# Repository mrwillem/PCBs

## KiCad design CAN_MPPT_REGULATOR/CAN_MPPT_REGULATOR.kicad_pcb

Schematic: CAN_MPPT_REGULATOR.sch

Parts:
AFF1: QBDS20zzzz; 7SEGMENT-LED_DUAL_QBDS200R
C1, C3, C4: C; C_0805
C2: 2nFC; C_0805
C5: 470nF; C_0805
C6, C34: 1uF; C_0805
C7, C8: 1uF 0805ZC105KAT2A; C_0805
C9: 2,2 uF; C_0805
C10, C18: 10nF; C_0603
C11, C14, C17, C21, C24, C25, C26, C27, C28, C29, C30, C35, C43, C44, C45, C46, C47, C72, C75: 100nF; C_0603
C12, C15: 2uF; C_0805
C13, C31: 4,7uF; C_0805
C16, C38: 33uF; CP_Elec_6.3x7.7
C19, C20: 22pF; C_0603
C22, C23: C; C_0603
C32: 2,2uF; C_0805
C33, C40, C42, C53: 1uF GRM219R71E105KA88D; C_0805
C36: C
C37: 100pF 60V; C_0805
C41: 10nF; C_0805
C51: 100nF; C_0805
C52: 1nF; C_0805
C60, C61, C62, C63: 10uF; C_0805
C70, C71, C73, C74: 4.7uF GRM31CR71H47; C_1206
CB1, CB2: 68 uF EEE-FK1J680UP; CP_Elec_8x10.5
CB3, CB4: B41888E8687M000; CP_Radial_D18.0mm_P7.50mm
CBIA1: 1 uF GRM219R71E105KA88D; C_0805
CBO1, CBO2: 100nF; C_0805
CCOMP1: 27nF 12065A272JAT2A; C_0805
CCOMP2: 47pF CL21C470JBANNNC; C_0805
CF1: 220nF C1608X5R1H224K080AB; C_0805
CIN1, CIN2, CIN3, CIN4, CIN5, CIN6, CIN7, CIN8, CIN9, CIN10: 10uF C3216X5R1H106K160AB; C_1206
COUT1, COUT2, COUT3, COUT4, COUT5, COUT6, COUT7, COUT8, COUT9, COUT10, COUT11, COUT12: 10 uF CL31A106MBHNNNE; C_1206
CSG1, CSG2, CSG3: 47pF 06035A470JAT2A; C_0603
CSL1: 91pF CL10C910JB8NCNC; C_0603
CSS1: 22nF gcm21b5c1h223ja16l; C_0805
CVCC1: 1 uF EMK107B7105KA-T; C_0603
D1, D6, D8: D_TVS; D_SMB
D2, D5, D9, D11, D12: D_Schottky_x2_Serial_AKC; SOT-23
D3: CMS06; D_MFLAT
D4: ZENER; D_SMA
D7: B240A-13-F; D_SMA
D10: D_Schottky_x2_ACom_KKA; SOT-23
D13, D14: LED; LED_0805
D15: D; SOD-323-Handsoldering
D16: ZENER; D_SOD-123
D17: ZENER
DBO1, DBO2: ZLLS400-QTA; D_SOD-323_HandSoldering
DF1: ZLLS400QTA; D_SOD-323_HandSoldering
F1: FUSE; Keystone_3557_2
J1: RJHSE-5380-02; RJHSE538X-02-noled
JP1: Jumper_NC_Small; NetTie0.4mmSMD
L1: PQ2614BHA-100K-ND; inductor_bourns_PQ2614BLA_BHA
L2: L; Choke_SMD_1206_Standard
P1: CONN_5X2; Pin_Header_Straight_2x05_Pitch1.27mm
P2, P3: CONN_01X02; Anderson_1336G1_2pole
P5, P6, P7, P8: CONN_01X01; hole
Q1, Q2, Q3, Q4: BSC027N06LS5; PG-TDSON-8-DGS
Q5: SQJQ100E-T1_GE3; PowerPAK_8x8L_DGS
Q6, Q7, Q8, Q9, Q10: 2N7002; SOT-323_SC-70
R1: 10K; R_0603_HandSolder
R2, R40: R; R_0805_HandSolder
R3: 10R; R_0805_HandSolder
R4, R8: 800K; R_0805_HandSolder
R5: 85K; R_0805_HandSolder
R6: 29K; R_0805_HandSolder
R7: 10K; R_0805_HandSolder
R9: 101K; R_0603_HandSolder
R10: 170K; R_0805_HandSolder
R11, R30: 500K; R_0805_HandSolder
R12, R16: 10R; R_0603_HandSolder
R13: 12K; R_0805_HandSolder
R14, R15: 2K; R_0603_HandSolder
R17: 20K; R_0603_HandSolder
R18, R19, R20, R21: 100R; R_0603_HandSolder
R22: 2M2 0,1%; R_0805_HandSolder
R23: 210K 0,1%; R_0805_HandSolder
R24: 300R; R_0603_HandSolder
R25, R27: 100K; R_0603_HandSolder
R26: 365K; R_0805_HandSolder
R28: 100K
R29: 2K2; R_0603_HandSolder
RCOMP1: 6.98K 1% CRCW04026K98FKED; R_0603_HandSolder
RCSG1: 100R 1%; R_0603_HandSolder
RF1: 10R 1%; R_0603_HandSolder
RFB1: 275K; R_0603_HandSolder
RFB2: 20K; R_0603_HandSolder
RMOD1: 93.1K 1% CRCW060393K1FKEA; R_0603_HandSolder
RN1: 100R; R_Cat16-8
RPG1: 20K; R_0603_HandSolder
RRT1: 267K 1% CRCW0402267KFKED; R_0603_HandSolder
RSNS1: WSHM28186L000FEA; VISHAY_WSHM_2812
RSP1: 100R 1%; R_0603_HandSolder
RUV1: 249K 1%; R_0603_HandSolder
RUV2: 154K 1%; R_0603_HandSolder
SiSS71DN2, SiSS71DN4: SiSS71DN; PowerPack1212-8S_Pitch0.65mm
U1, U6: ACS725; SO-8_5.3x6.2mm_Pitch1.27mm
U2: LTC4366-2; SOT23-8
U3, U4: LTC3245; MSOP-12-1EP_3x4mm_Pitch0.65mm
U5: 8MHz; Crystal_SMD_EuroQuartz_MT-4pin_3.2x2.5mm_hand
U7: LM74610; VSSOP-8_2.4x2.1mm_Pitch0.5mm
U8, U9: MCP3427; MSOP-10_3x3mm_Pitch0.5mm
U10: USB-CMC-Wuerth; CMC-SMD-Wuerth
U11: LM5175; TSSOP-28-1EP_4.4x9.7mm_Pitch0.65mm
U12: STM32L433CC; LQFP-48_7x7mm_Pitch0.5mm
U13: MCP4726; SOT-23-6_Handsoldering
U14: TCAN330; SOIC-8_3.9x4.9mm_Pitch1.27mm
U15: ADUM1402; SOIC-16W_7.5x10.3mm_Pitch1.27mm
U16: PCA9536; VSSOP-8_3.0x3.0mm_Pitch0.65mm
U17: LTC1540; MSOP-8_3x3mm_Pitch0.65mm

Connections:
24VPGOOD: R11.1, U3.8 (PGOOD), U12.17 (PA7/TIM1_CH1N/I2C3_SCL/SPI1_MOSI/QUADSP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)
24VVIN: C4.1, C16.1, C73.1, C74.1, C75.1, R2.1, U3.1 (VIN), U3.2 (VIN), U3.3 (VIN), U3.5 (SEL1), U3.6 (SEL2)
+3.3V: C11.2, C12.2, C13.1, C14.2, C15.2, C17.2, C21.2, C22.1, C23.1, C24.1, C25.1, C26.1, C27.1, C29.1, C30.1, C31.1, C32.1, C33.1, C40.1, C41.1, C46.1, C51.1, C52.1, C53.1, C62.2, C63.2, D2.2 (K), D5.2 (K), D9.2 (K), D11.2 (K), D12.2 (K), P1.1, R1.1, R11.2, R14.1, R15.1, R40.2, RPG1.2, U1.8 (VCC), U3.7 (OUTS/ADJ), U3.10 (VOUT), U6.8 (VCC), U8.6 (VDD), U9.6 (VDD), U9.9 (AD0), U9.10 (AD1), U12.1 (VBAT), U12.9 (VDDA/VREF+), U12.24 (VDD), U12.36 (VDD_USB), U12.48 (VDD), U13.3 (VDD), U13.6 (VREF), U15.1 (VDD1), U16.8 (VCC)
A: AFF1.12 (A2), AFF1.17 (A1), RN1.11 (R6.2)
B: AFF1.11 (B2), AFF1.16 (B1), RN1.12 (R5.2)
C: AFF1.4 (C1), AFF1.9 (C2), RN1.15 (R2.2)
CANPGOOD: R30.2, U4.8 (PGOOD), U15.10 (VE2), U15.11 (NC)
CANPREDIODE: D4.1 (K), R6.2, SiSS71DN2.5 (D), SiSS71DN2.6 (D), SiSS71DN2.7 (D), SiSS71DN2.8 (D), SiSS71DN4.1 (S), SiSS71DN4.2 (S), SiSS71DN4.3 (S)
CANRX: U12.45 (PB8/I2C1_SCL/CAN1_RX/LCD_SEG16/SDMMC1_D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), U15.5 (VOC)
CANSHLD: J1.6, J1.14, J1.17 (SHIELD)
CANSLEEP: U12.12 (PA2/TIM2_CH3/USART2_TX/LPUART1_TX/QUADS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), U15.3 (VIA)
CANTX: U12.46 (PB9/R_OUT/I2C1_SDA/SPI2_NSS/CAN1_TX/LCD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), U15.4 (VIB)
CANVIN: C5.1, C38.1, C70.1, C71.1, C72.1, R13.2, SiSS71DN2.1 (S), SiSS71DN2.2 (S), SiSS71DN2.3 (S), U2.7 (OUT), U4.1 (VIN), U4.2 (VIN), U4.3 (VIN), U4.5 (SEL1), U4.6 (SEL2)
CANVOUT: C42.1, C44.2, C47.1, C60.2, C61.2, R30.1, U4.7 (OUTS/ADJ), U4.10 (VOUT), U14.3 (VCC), U15.16 (VDD2)
CAN_PGOOD: U15.6 (NC), U16.5 (P3)
CATHODE: C1.2, L2.2, Q5.1 (D), R4.1, U1.1 (IP+), U1.2 (IP+), U7.8 (GND)
CSG1: C34.2, C35.2, C36.1, CB1.2, CB2.2, CB3.2, CB4.2, CBIA1.2, CIN1.2, CIN2.2, CIN3.2, CIN4.2, CIN5.2, CIN6.2, CIN7.2, CIN8.2, CIN9.2, CIN10.2, COUT1.2, COUT2.2, COUT3.2, COUT4.2, COUT5.2, COUT6.2, COUT7.2, COUT8.2, COUT9.2, COUT10.2, COUT11.2, COUT12.2, CVCC1.2, D1.2 (A2), D8.2 (A2), D16.2 (A), D17.2 (A), JP1.1, P2.1, P3.1, Q9.2 (S), Q10.2 (S), R5.2, R10.2, R18.1, R20.1, R23.2, RCSG1.2, RSNS1.2, U11.22 (PGND), U17.1 (GND), U17.2 (V-)
D: AFF1.2 (D1), AFF1.7 (D2), RN1.14 (R3.2)
DGND: C1.1, C3.1, C4.2, C10.1, C11.1, C12.1, C13.2, C14.1, C15.1, C16.2, C17.1, C18.1, C19.1, C20.1, C21.1, C22.2, C23.2, C24.2, C25.2, C26.2, C27.2, C28.2, C29.2, C30.2, C31.2, C32.2, C33.2, C40.2, C41.2, C46.2, C51.2, C52.2, C53.2, C62.1, C63.1, C73.2, C74.2, C75.2, CCOMP1.1, CCOMP2.1, CF1.2, CSL1.2, CSS1.1, D2.1 (A), D5.1 (A), D9.1 (A), D11.1 (A), D12.1 (A), D14.1 (K), JP1.2, P1.3, P1.5, P1.7, P1.9, Q6.2 (S), Q7.2 (S), Q8.2 (S), R7.1, RFB2.2, RMOD1.2, RRT1.2, RUV2.2, U1.5 (GND), U3.4 (BURST), U3.12 (GND), U3.13 (GND), U5.2 (GND), U5.4 (GND), U6.5 (GND), U8.3 (VSS), U8.5 (CH2-), U8.9 (AD0), U8.10 (AD1), U9.3 (VSS), U9.5 (CH2-), U11.5 (DITH), U11.10 (AGND), U11.29 (THERMAL), U12.8 (VSSA/VREF-), U12.23 (VSS), U12.35 (VSS), U12.47 (VSS), U13.2 (VSS), U15.2 (GND1), U15.8 (GND1), U16.4 (GND)
DIG1: R12.2, U12.40 (PB4/NJTRST/I2C3_SDA/SPI1_MISO/SPI3_MISO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)
DIG1_MOS: AFF1.8 (CC2), Q7.3 (D)
DIG2: R16.2, U12.41 (PB5/PTIM1_IN1/I2C1_SMBA/SPI1_MOSI/SPI3_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)
DIG2_MOS: AFF1.3 (CC1), Q8.3 (D)
DP: AFF1.5 (DP1), AFF1.10 (DP2), RN1.16 (R1.2)
E: AFF1.1 (E1), AFF1.6 (E2), RN1.13 (R4.2)
ECANH: J1.1, J1.9, U10.1 (D+In)
ECANL: J1.2, J1.10, U10.4 (D-In)
ECANV+: C37.1, D6.1 (A1), J1.8, J1.16, SiSS71DN4.5 (D), SiSS71DN4.6 (D), SiSS71DN4.7 (D), SiSS71DN4.8 (D)
EN_SMPS: Q6.3 (D), Q9.3 (D), RUV1.2, RUV2.1, U11.1 (EN/UVLO)
EXTRESET: C28.1, P1.10, U12.7 (NRST)
F: AFF1.14 (F2), AFF1.19 (F1), RN1.9 (R8.2)
FB: R9.1, RFB1.2, RFB2.1, U11.11 (FB)
G: AFF1.15 (G2), AFF1.20 (G1), RN1.10 (R7.2)
GNDD: C2.1, C37.2, C38.2, C42.2, C43.2, C44.1, C45.2, C47.2, C60.1, C61.1, C70.2, C71.2, C72.2, D6.2 (A2), D10.3 (A), J1.3, J1.7, J1.11, J1.15, R26.1, R27.1, R29.1, U4.4 (BURST), U4.12 (GND), U4.13 (GND), U14.2 (GND), U15.9 (GND2), U15.15 (GND2)
HDRV1: Q1.2 (G), U11.27 (HDRV1)
HDRV2: Q2.2 (G), U11.19 (HDRV2)
IIN: U1.7 (VIOUT), U8.4 (CH2+)
IOUT: U6.7 (VIOUT), U9.4 (CH2+)
LDRV1: Q3.2 (G), U11.25 (LDRV1)
LDRV2: Q4.2 (G), U11.21 (LDRV2)
unnamed: C2.2, R3.1, U2.8 (GATE)
unnamed: C3.2, L2.1, R2.2
unnamed: C5.2, C6.1, R29.2, U2.4 (VSS), U2.5 (BASE)
unnamed: C6.2, U2.3 (TIMER)
unnamed: C7.1, U3.9 (C+)
unnamed: C7.2, U3.11 (C-)
unnamed: C8.1, U4.9 (C+)
unnamed: C8.2, U4.11 (C-)
unnamed: C9.1, U7.7 (VCAP+)
unnamed: C9.2, U7.1 (VCAPL)
unnamed: C10.2, U1.6 (FILTER)
unnamed: C18.2, U6.6 (FILTER)
unnamed: C19.2, U5.1 (OSC), U12.6 (PH1/OSC_OUT)
unnamed: C20.2, U5.3 (OSC), U12.5 (PH0/OSC_IN)
unnamed: C34.1, Q9.1 (G), Q10.1 (G), U17.8 (OUT)
unnamed: C35.1, D15.1 (K), U17.7 (V+)
unnamed: C36.2, R22.1, R28.2
unnamed: C43.1, D10.2 (K), U10.2 (D+Out), U14.7 (CANH)
unnamed: C45.1, D10.1 (K), U10.3 (D-Out), U14.6 (CANL)
unnamed: CBO1.2, DBO1.1 (K), U11.26 (BOOT1)
unnamed: CBO2.1, DBO2.1 (K), U11.20 (BOOT2)
unnamed: CCOMP1.2, RCOMP1.2
unnamed: CCOMP2.2, RCOMP1.1, U11.9 (COMP)
unnamed: CF1.1, RF1.2, U11.2 (VIN)
unnamed: CSG1.1, RSP1.1, U11.16 (CS)
unnamed: CSG1.2, RCSG1.1, U11.15 (CSG)
unnamed: CSG2.1, D5.3 (common), R21.2, U8.1 (CH1+)
unnamed: CSG2.2, D12.3 (common), R20.2, U8.2 (CH1-)
unnamed: CSG3.1, D9.3 (common), R19.1, U9.1 (CH1+)
unnamed: CSG3.2, D11.3 (common), R18.2, U9.2 (CH1-)
unnamed: CSL1.1, U11.7 (SLOPE)
unnamed: CSS1.2, U11.8 (SS)
unnamed: CVCC1.1, DBO1.2 (A), DBO2.2 (A), U11.23 (VCC)
unnamed: D2.3 (common), R9.2, U13.1 (VOUT)
unnamed: D4.2 (A), R27.2, SiSS71DN4.4 (G)
unnamed: D13.1 (K), Q10.3 (D)
unnamed: D13.2 (A), R24.1
unnamed: D14.2 (A), R40.1
unnamed: D15.2 (A), D16.1 (K), R25.1
unnamed: D17.1 (K), R17.1, R24.2
unnamed: DF1.1 (K), RF1.1
unnamed: Q5.2 (G), U7.2 (GATEPD), U7.6 (GATE)
unnamed: Q6.1 (G), R1.2, U16.1 (P0)
unnamed: Q7.1 (G), R12.1
unnamed: Q8.1 (G), R16.1
unnamed: R3.2, SiSS71DN2.4 (G)
unnamed: R6.1, U2.1 (VDD), U2.2 (SD)
unnamed: R7.2, U12.44 (PH3/BOOT0)
unnamed: R8.2, R10.1, R19.2
unnamed: R13.1, R26.2, U2.6 (FB)
unnamed: R4.2, R5.1, R21.1
unnamed: R22.2, R23.1, U17.3 (IN+)
unnamed: RMOD1.1, U11.4 (MODE)
unnamed: RN1.1 (R1.1), U12.31 (PA10/TIM1_CH3/I2C1_SDA/USART1_RX/USB_CR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)
unnamed: RN1.2 (R2.1), U12.32 (PA11/TIM1_CH4/TIM1_BKIN2/SPI1_MISO/USAR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)
unnamed: RN1.3 (R3.1), U12.30 (PA9/IM1_CH2/I2C1_SCL/USART1_TX/LCD_COM1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)
unnamed: RN1.4 (R4.1), U12.29 (PA8/MCO/TIM1_CH1/USART1_CK/LCD_COM0/SWP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)
unnamed: RN1.5 (R5.1), U12.28 (PB15/RTC_REFIN/TIM1_CH3N/SPI2_MOSI/TSC_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)
unnamed: RN1.6 (R6.1), U12.27 (PB14/TIM1_CH2N/I2C2_SDA/SPI2_MISO/USART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)
unnamed: RN1.7 (R7.1), U12.26 (PB13/TIM1_CH1N/I2C2_SCL/SPI2_SCK/USART3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)
unnamed: RN1.8 (R8.1), U12.25 (PB12/TIM1_BKIN/TIM1_BKIN_COMP2/I2C2_SMB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)
unnamed: RRT1.1, U11.6 (RT)
unnamed: U11.13 (ISNS-), U11.14 (ISNS+)
unnamed: U14.1 (TXD), U15.13 (VOB)
unnamed: U14.4 (RXD), U15.12 (VIC)
unnamed: U14.8 (S), U15.14 (VOA)
unnamed: U17.4 (IN-), U17.5 (HYST), U17.6 (REF)
OUTRAIL: CB3.1, CB4.1, CBIA1.1, COUT1.1, COUT2.1, COUT3.1, COUT4.1, COUT5.1, COUT6.1, COUT7.1, COUT8.1, COUT9.1, COUT10.1, COUT11.1, COUT12.1, D3.1 (K), Q2.1 (D), RFB1.1, U6.1 (IP+), U6.2 (IP+), U11.12 (VOSNS), U11.24 (BIAS)
RCS1: D7.2 (A), Q3.3 (S), Q4.3 (S), RSNS1.1, RSP1.2
SCL: R14.2, U8.8 (SCL), U9.8 (SCL), U12.21 (PB10/TIM2_CH3/I2C2_SCL/SPI2_SCK/USART3_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), U13.5 (SCL), U16.6 (SCL)
SDA: R15.2, U8.7 (SDA), U9.7 (SDA), U12.22 (PB11/TIM2_CH4/I2C2_SDA/USART3_RX/LPUART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), U13.4 (SDA), U16.7 (SDA)
SMPS_PGOOD: RPG1.1, U11.17 (PGOOD), U16.2 (P1)
SW1: CBO1.1, D7.1 (K), L1.1, Q1.3 (S), Q3.1 (D), U11.28 (SW1)
SW2: CBO2.2, D3.2 (A), L1.2, Q2.3 (S), Q4.1 (D), U11.18 (SW2)
SWCLK: P1.4, U12.37 (PA14/JTCK-SWCLK/LPTIM1_OUT/I2C1_SMBA/SW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)
SWDIO: P1.2, U12.34 (PA13/TMS-SWDIO/IR_OUT/USB_NOE/SWPMI1_TX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)
SWO: P1.6, U12.39 (PB3/JTDO-TRACESWO/TIM2_CH2/SPI1_SCK/SPI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)
VBAT: D8.1 (A1), P3.2, R8.1, R17.2, R25.2, R28.1, U6.3 (IP-), U6.4 (IP-)
VBULK: CB1.1, CB2.1, CIN1.1, CIN2.1, CIN3.1, CIN4.1, CIN5.1, CIN6.1, CIN7.1, CIN8.1, CIN9.1, CIN10.1, DF1.2 (A), Q1.1 (D), RUV1.1, U1.3 (IP-), U1.4 (IP-), U11.3 (VISNS)
VFUSED: F1.1, Q5.3 (S), U7.4 (Anode)
VIN: D1.1 (A1), F1.2, P2.2

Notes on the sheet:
Mounting Holes

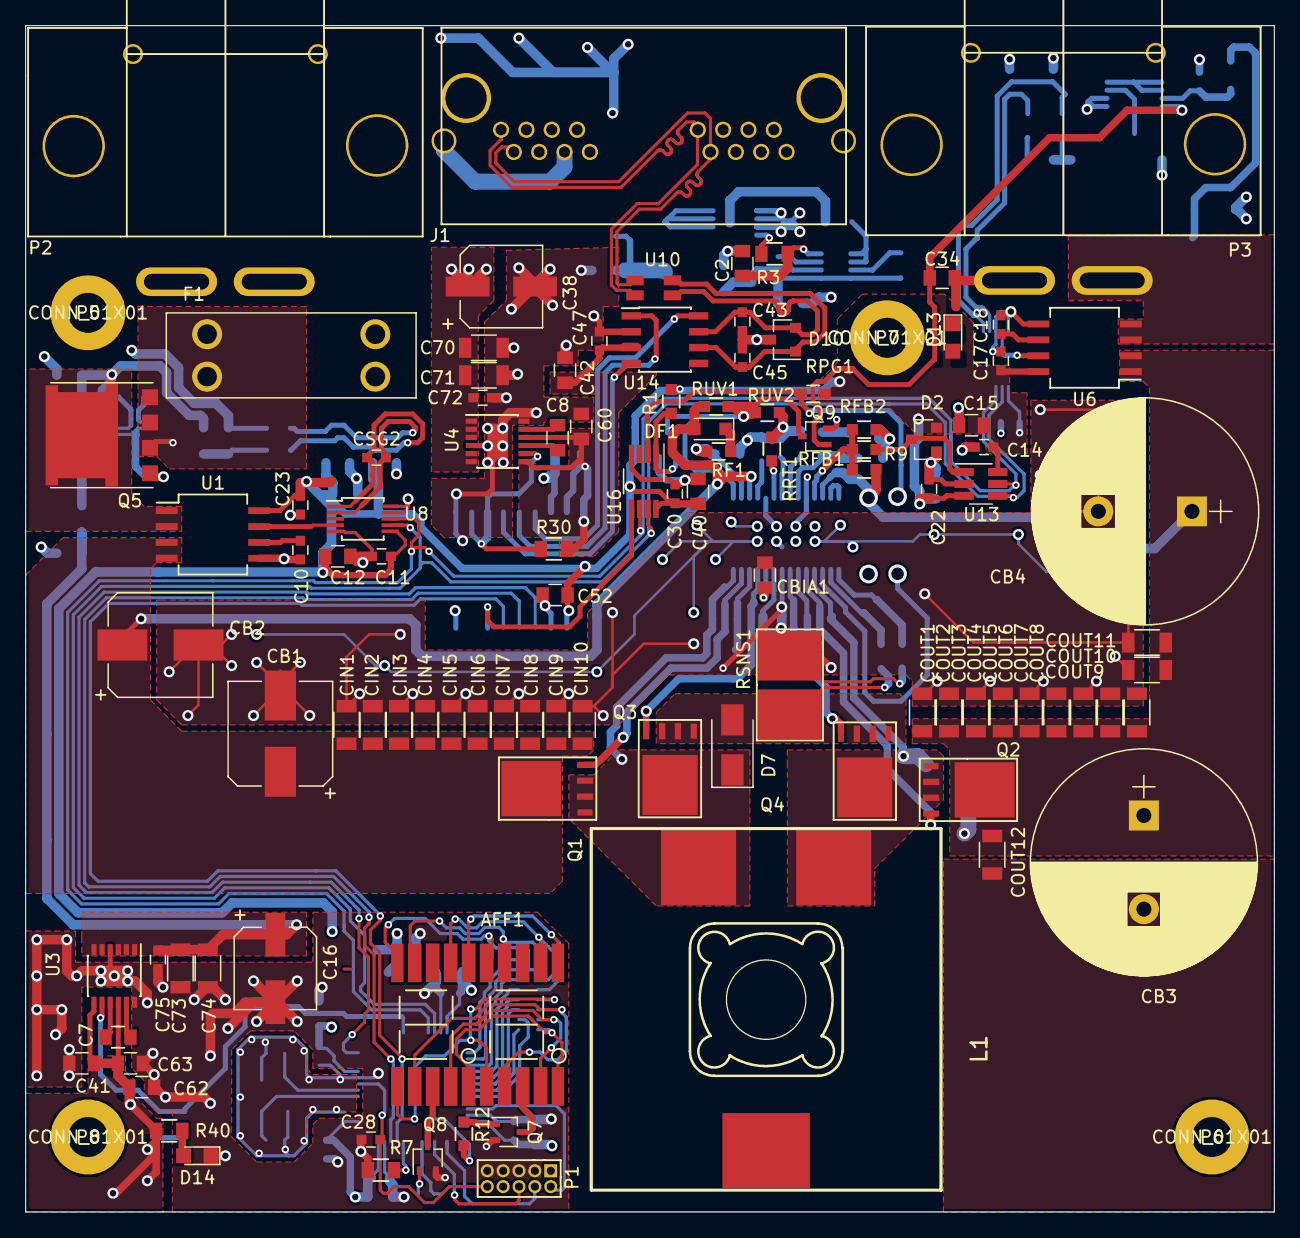
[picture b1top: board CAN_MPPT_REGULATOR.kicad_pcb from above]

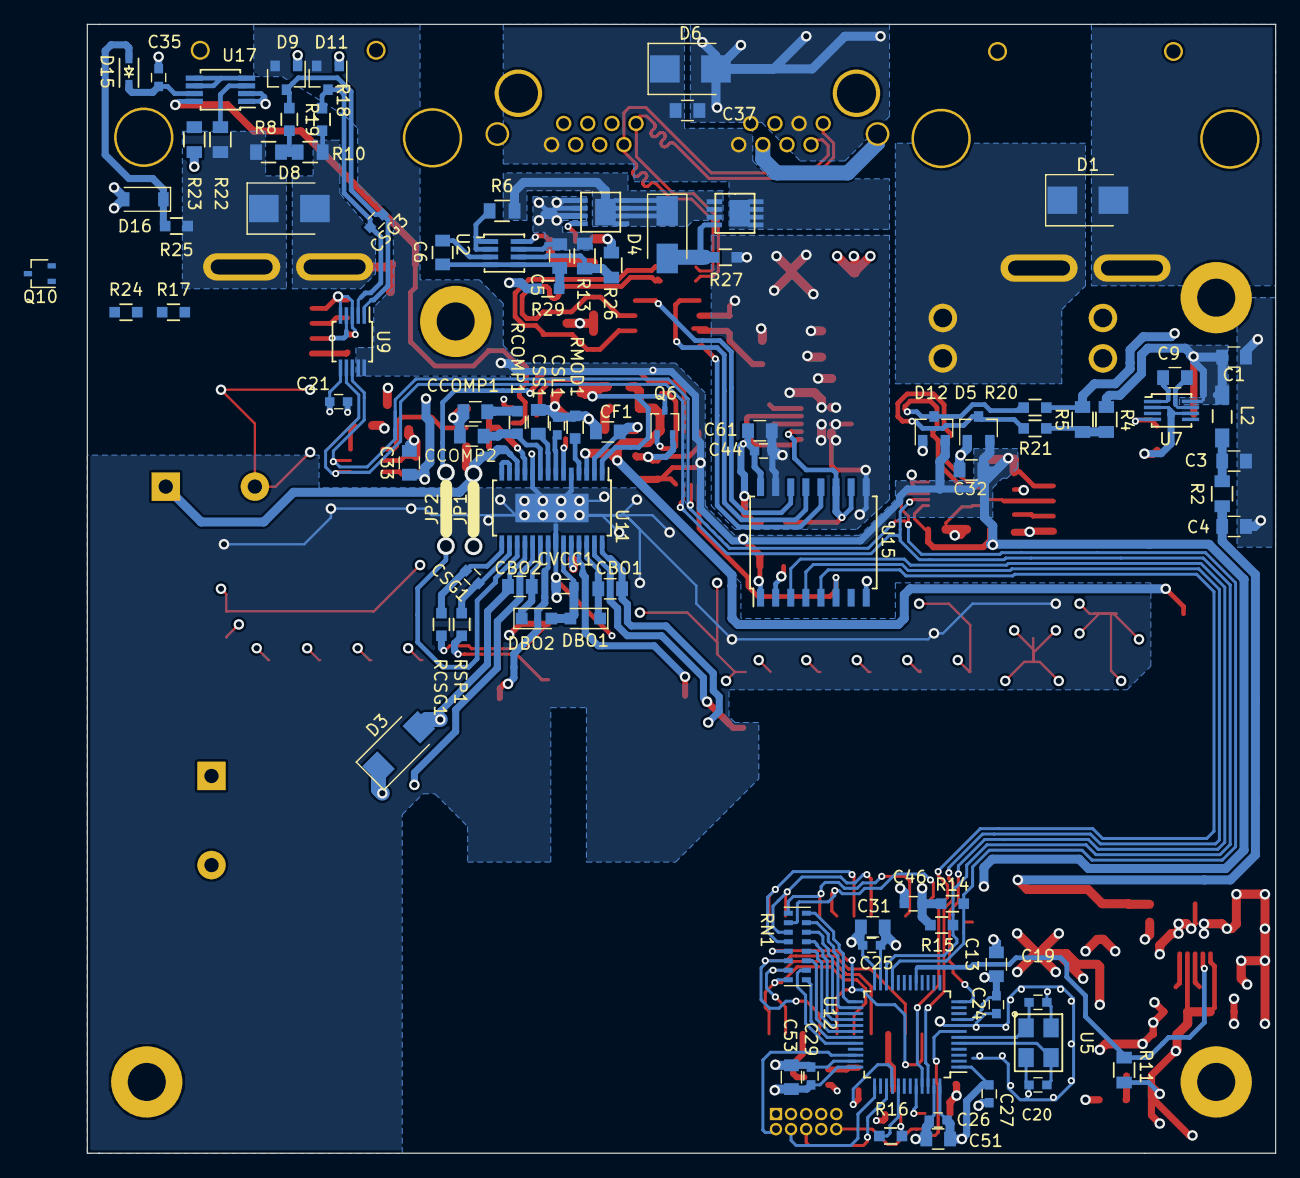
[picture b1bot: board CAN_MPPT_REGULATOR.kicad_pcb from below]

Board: 6 copper layers, 100.0 x 95.0 mm, 200 parts (90 on the bottom side), 120 nets.

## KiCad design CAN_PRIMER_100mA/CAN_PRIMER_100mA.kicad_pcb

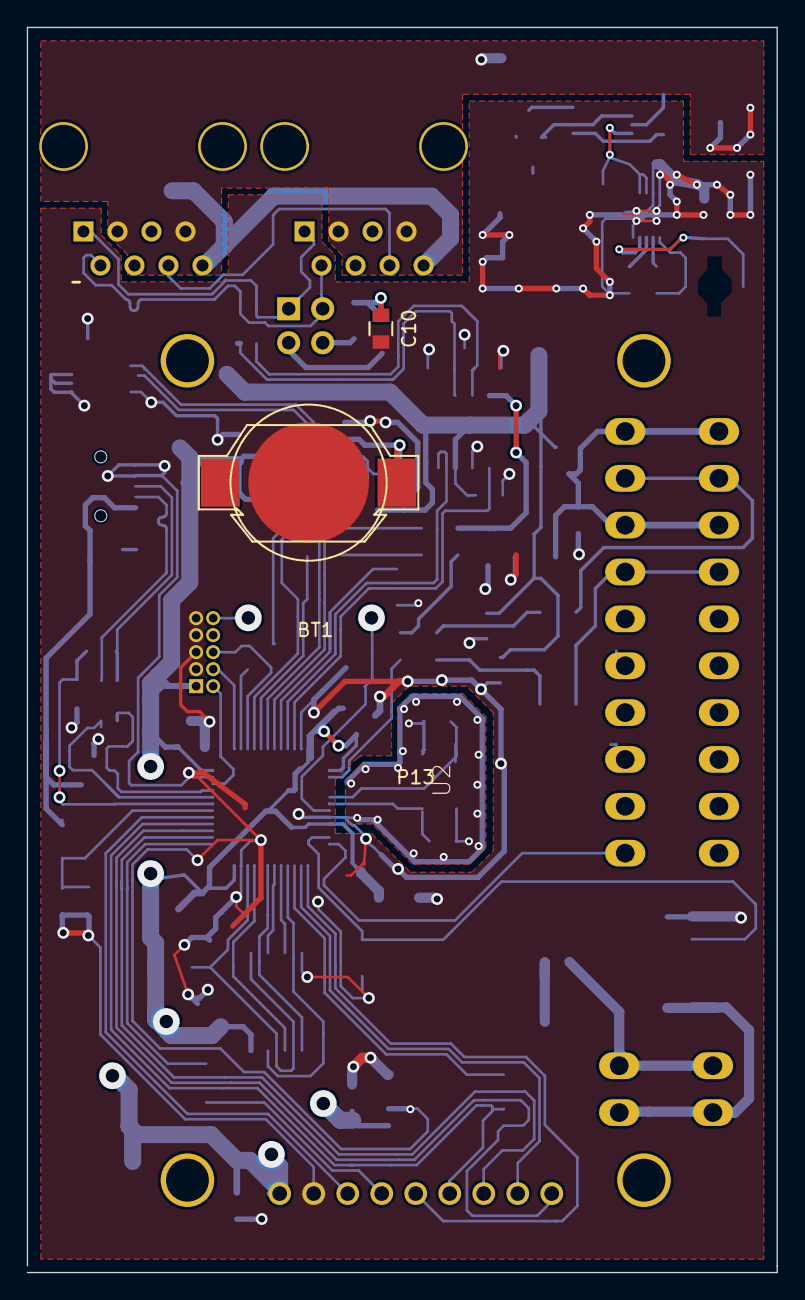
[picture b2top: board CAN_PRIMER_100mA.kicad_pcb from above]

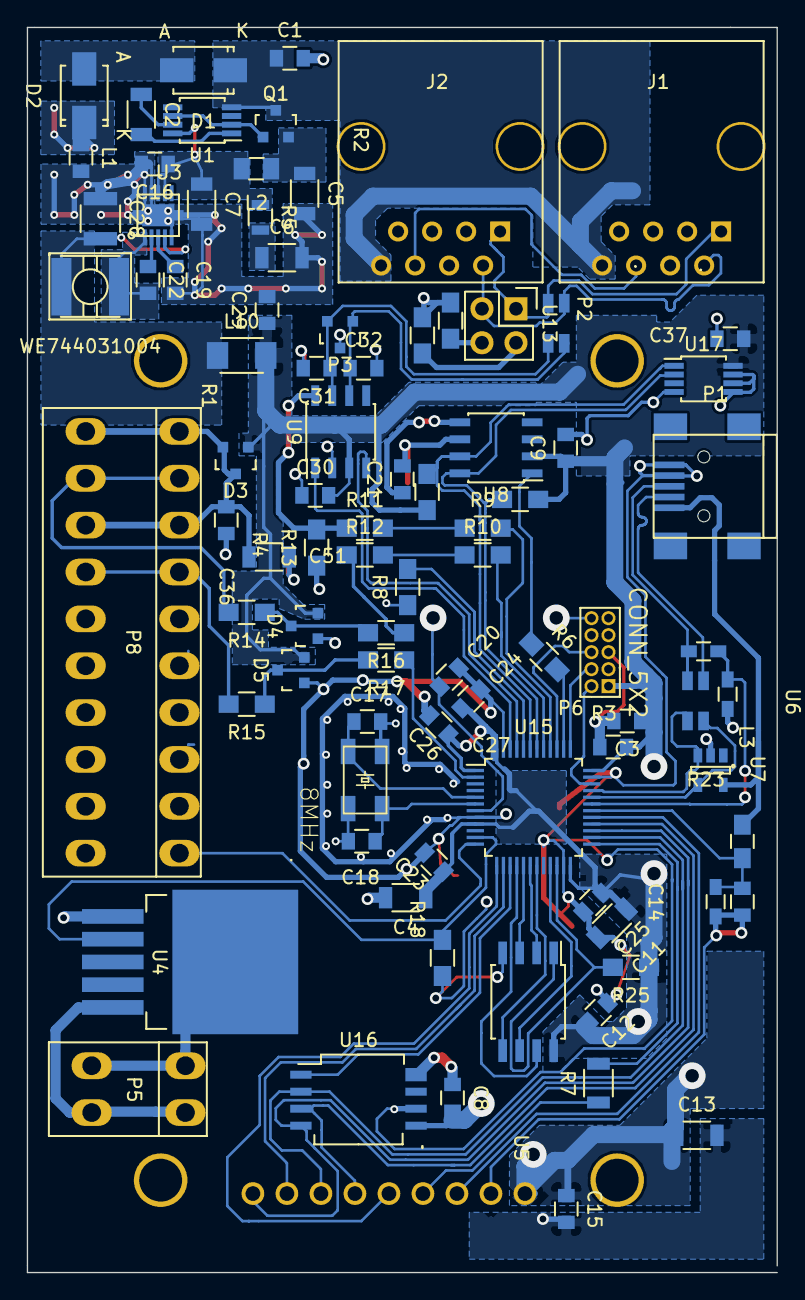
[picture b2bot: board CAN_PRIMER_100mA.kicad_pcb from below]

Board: 4 copper layers, 56.0 x 93.0 mm, 92 parts (89 on the bottom side), 76 nets.

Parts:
BT1: Battery; BatterieHolderCR1025_SMD
C1: 100pF 60V; C_0805
C2: 2.2 uF; C_1206
C3: 2,2uF; C_0805
C4, C13: 4,7uF; C_1206
C5, C6, C7: 4.7uF GRM31CR71H47; C_1206
C8, C9, C10, C12, C14, C15, C16, C20, C22, C23, C24, C25, C26, C27, C30, C31, C32, C36, C37: 100nF; C_0805
C11: 2,2uF; C_1206
C17, C18: 22pF; C_0805
C19: 1uF 0805ZC105KAT2A; C_0805
C21: 10nF; C_0805
C28: 22uF; C_1210
C29: 1uF GRM219R71E105KA88D; C_0805
C51: 10uF; C_1206
D1, D2: ZENER; SMA_Standard
D3: BAS70-G; SOT-23
D4, D5: BAS70-04-G; SOT-23
J1, J2: RJ45; RJ45_8
JP1: Jumper_NC_Small; NetTie-I_Connected_SMD
L1: L_Small; C_0805
L2: 1uH MLP2016V1R0MT; Choke_SMD_2016_Standard
L3: INDUCTOR; C_0805_HandSoldering
L10: 100nHNLCV32-PFR1; Choke_SMD_3225_Standard
P1: USB_B; USB_Mini-B
P2: CONN_02X02; Pin_Header_Straight_2x02
P3: CONN_01X03; SOT-23
P5: CONN_01X02; weidmueller_2
P6: CONN_5X2; Pin_Header_Straight_2x05_Pitch1.27mm
P8: CONN_5X2; weidmueller_10
P13: DISPLAY; 2.2inchQVGASPIwithStorage
Q1: SQ2362ES; SOT-23
R1, R2: 60R; R_0805_HandSoldering
R3, R4: 2K; R_0805_HandSoldering
R5: 100 mR ERJ-3RQFR10V; R_0805
R6, R9, R10, R11, R12: 0R0; R_0805_HandSoldering
R7: 0R0; R_1206
R8, R13, R18: 10K; R_0805_HandSoldering
R14, R15: 1K; R_0805_HandSoldering
R16, R17: 10R; R_0805_HandSoldering
R21, R24: 47K; R_0603_HandSoldering
R23: 1K5; R_0603_HandSoldering
R25: 100K; R_0805_HandSoldering
U1: LM74610; MSOP-8_3x3mm_Pitch0.65mm
U2: 8MHz; Xtal_Ceramic_5x3.2
U3: LM53601-Q1; VSON10_Thermal_Pad
U4: BTS410; TO-263-5Lead
U5: S25FL127S; SOIJ-8_5.3x5.3mm_Pitch1.27mm
U6, U13: USB-CMC-Wuerth; CMC-SMD-Wuerth
U7: TVS-ARRAY-SOT5; SOT-23-5
U8: DS3231; SOIC-8_3.9x4.9mm_Pitch1.27mm
U9: SN65HVD233; SOIC-8_3.9x4.9mm_Pitch1.27mm
U15: STM32L433CC; LQFP-48_7x7mm_Pitch0.5mm
U16: KP25x; PG-DSOF-8-16_7x7mm_Pitch1.27mm
U17: MCP9808; MSOP-8_3x3mm_Pitch0.65mm
WE744031004: 4.7 uH; Choke_SMD_4.3x4.3_H3

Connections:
+36V: C5.1, L2.1, Q1.2
CANRX: U9.4, U15.45
CANSHLD: J1.6, J2.6
CANSLEEP: R11.1, R13.2, U9.8
CANTX: U9.1, U15.46
DGND: BT1.2, C3.2, C4.2, C5.2, C6.2, C7.2, C8.1, C9.2, C10.2, C11.2, C12.1, C13.2, C14.1, C15.2, C16.2, C19.2, C20.2, C21.1, C23.2, C24.2, C25.2, C26.2, C27.2, C28.1, C29.2, C30.1, C31.2, C32.2, C36.2, C37.2, C51.2, D4.1, D5.1, JP1.1, L1.2, P1.4, P1.5, P3.3, P6.3, P6.5, P6.7, P6.9, P13.2, R8.1, R13.1, R18.2, R21.1, R24.1, U3.5, U3.9, U3.10, U3.11, U4.1, U5.4, U7.2, U8.5, U9.2, U15.8, U15.23, U15.35, U15.47, U16.6, U16.8, U17.4, U17.5, U17.6, U17.7
DISCONNECT: R23.1, R24.2, U15.31
DISPCS: P13.3, U15.29
DISPDC: P13.5, U15.13
DISPRESET: P13.4, R7.1
ECANBETWEEN: D1.2, D2.2
ECANGND: C1.2, D2.1, J1.3, J1.7, J2.3, J2.7, L1.1
ECANH: J1.1, J2.1, P2.1, U13.1
ECANL: J1.2, J2.2, P2.3, U13.4
ECANV+: C1.1, D1.1, J1.8, J2.8, Q1.3, U1.4
EXTRESET: C20.1, P6.10, U15.7
LED: P13.8, U15.14
MEMCS: R25.2, U5.1, U15.22
MISO: P13.9, U15.27, U16.4
MOS2: R18.1, U4.2, U15.11
MOSI: P13.6, U15.28, U16.3
unnamed: BT1.1, C21.2, U8.6
unnamed: C2.1, U1.7
unnamed: C2.2, U1.1
unnamed: C10.1, R1.2, R2.1
unnamed: C17.2, U2.3, U15.5
unnamed: C18.2, U2.1, U15.6
unnamed: C19.1, U3.3
unnamed: C22.1, U3.2
unnamed: C31.1, P3.2, U9.7, U13.2
unnamed: C32.1, P3.1, U9.6, U13.3
unnamed: C36.1, C51.1, D3.2, D3.3, P8.1, P8.3, P8.5
unnamed: D4.3, R14.1, R16.2
unnamed: D5.3, R15.1, R17.2
unnamed: P1.2, U6.4
unnamed: P1.3, R23.2, U6.1
unnamed: P2.2, R1.1
unnamed: P2.4, R2.2
unnamed: P5.1, U4.3
unnamed: P5.2, U4.5
unnamed: P8.2, R14.2
unnamed: P8.4, R15.2
unnamed: Q1.1, U1.2, U1.6
unnamed: R6.2, U15.38
unnamed: R7.2, U15.25
unnamed: R8.2, U15.44
unnamed: R9.2, U15.40
unnamed: R10.1, R12.2
unnamed: R10.2, U15.41
unnamed: R9.1, R11.2
PRESURECS: U15.15, U16.1
QUADCLK: U5.6, U15.21
QUADIO0: U5.5, U15.19
QUADIO1: U5.2, U15.18
QUADIO2: U5.3, U15.17
QUADIO3: U5.7, U15.16
SCK: P13.7, U15.26, U16.2
SCL: R3.2, U8.8, U15.42, U17.2
SDA: R4.2, U8.7, U15.43, U17.1
SWCLK: P6.4, U15.37
SWDIO: P6.2, U15.34
SWITCH1: R12.1, R16.1
SWITCH2: R17.1, U15.2
SWITCH3: P8.10, U15.12
SWO: P6.6, U15.39
TIMERCLK: R6.1, U8.1
USBCONNECTED: C14.2, L3.1, R21.2, U15.30
USBD+: U6.2, U7.3, U15.33
USBD-: U6.3, U7.4, U15.32
USBVCC: L3.2, P1.1, U7.5
VCC: C3.1, C4.1, C8.2, C9.1, C11.1, C12.2, C13.1, C15.1, C23.1, C24.1, C25.1, C26.1, C27.1, C29.1, C30.2, C37.1, D3.1, D4.2, D5.2, L10.2, P6.1, P13.1, R3.1, R4.1, R25.1, U5.8, U8.2, U9.3, U15.1, U15.9, U15.24, U15.36, U15.48, U16.5, U17.8
VCCUNFILTERED: C28.2, L10.1, U3.4, WE744031004.2
VIN: C7.1, C16.1, L2.2, R5.1, U1.8, U3.7, U3.8
VRES: C6.1, R5.2
VSW: C22.2, U3.1, WE744031004.1
stmxtalgnd: C17.1, C18.1, JP1.2, U2.2, U2.4
